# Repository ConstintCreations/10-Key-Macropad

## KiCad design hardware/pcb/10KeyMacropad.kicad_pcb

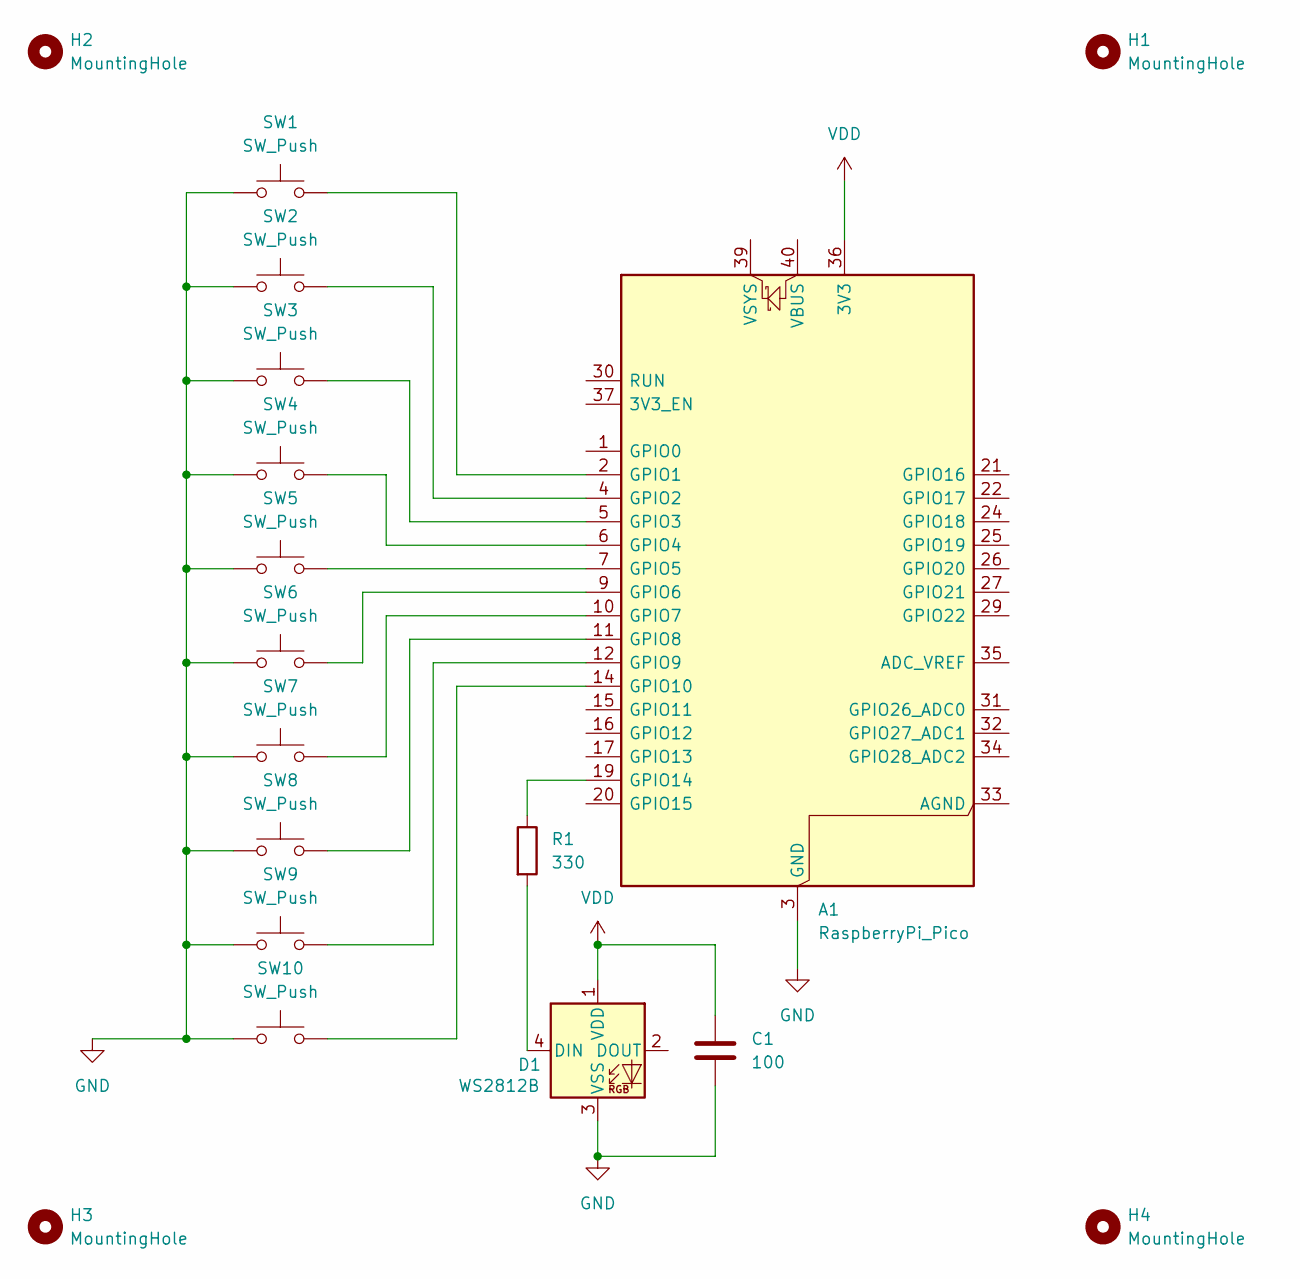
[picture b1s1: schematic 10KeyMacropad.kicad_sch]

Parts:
A1: RaspberryPi_Pico; PinHeader_2x20_P2.54mm_Vertical
C1: 100; CP_Radial_D5.0mm_P2.00mm
D1: WS2812B; LED_WS2812B_PLCC4_5.0x5.0mm_P3.2mm
H1, H2, H3, H4: MountingHole; MountingHole_3.2mm_M3
R1: 330; R_Axial_DIN0207_L6.3mm_D2.5mm_P10.16mm_Horizontal
SW1, SW2, SW3, SW4, SW5, SW6, SW7, SW8, SW9, SW10: SW_Push; MX-Hotswap-1U

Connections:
GND: A1.3 (GND), A1.8 (GND), A1.13 (GND), A1.18 (GND), A1.23 (GND), A1.28 (GND), A1.38 (GND), C1.2, D1.3 (VSS), SW1.1, SW2.1, SW3.1, SW4.1, SW5.1, SW6.1, SW7.1, SW8.1, SW9.1, SW10.1
unnamed: A1.2 (GPIO1), SW1.2
unnamed: A1.4 (GPIO2), SW2.2
unnamed: A1.5 (GPIO3), SW3.2
unnamed: A1.6 (GPIO4), SW4.2
unnamed: A1.7 (GPIO5), SW5.2
unnamed: A1.9 (GPIO6), SW6.2
unnamed: A1.10 (GPIO7), SW7.2
unnamed: A1.11 (GPIO8), SW8.2
unnamed: A1.12 (GPIO9), SW9.2
unnamed: A1.14 (GPIO10), SW10.2
unnamed: A1.19 (GPIO14), R1.1
unnamed: D1.4 (DIN), R1.2
VDD: A1.36 (3V3), C1.1, D1.1 (VDD)

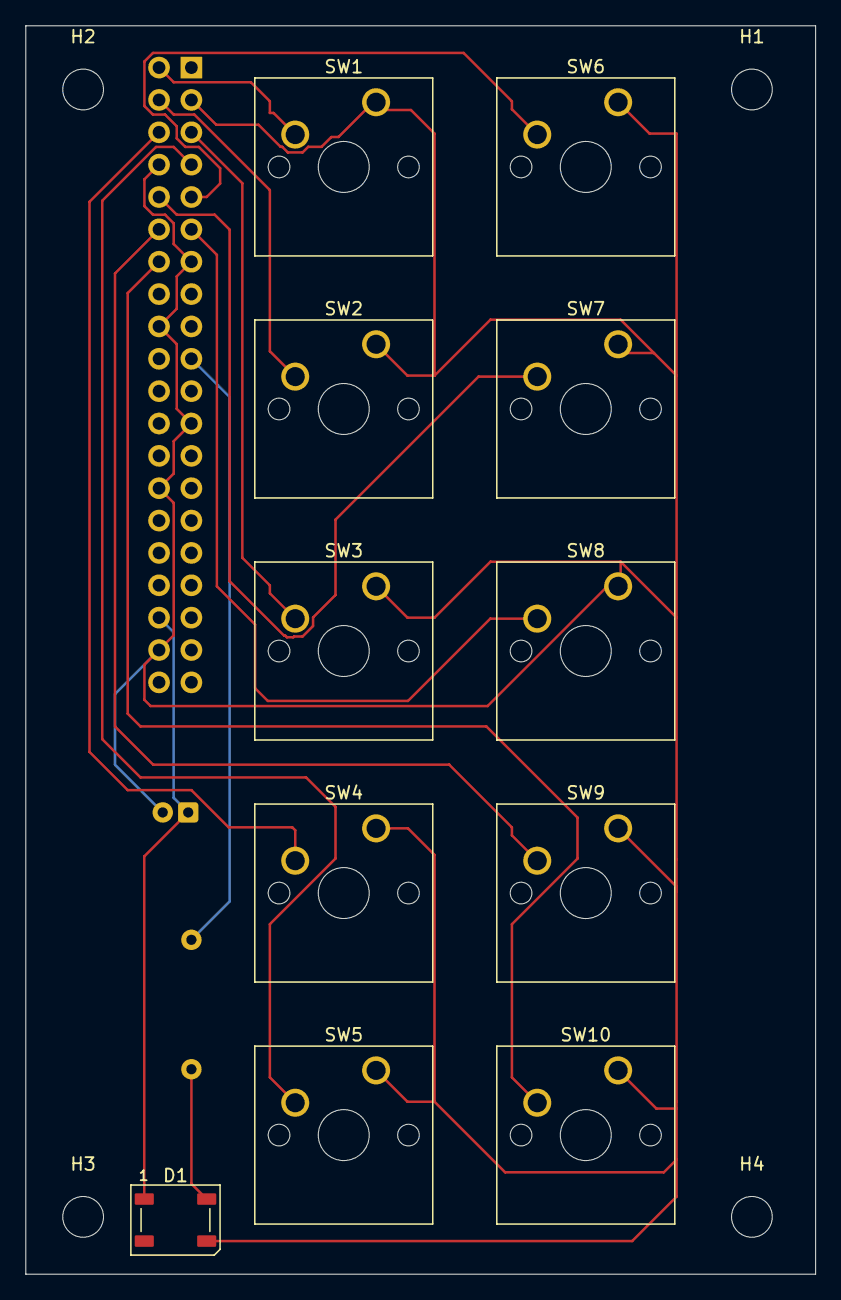
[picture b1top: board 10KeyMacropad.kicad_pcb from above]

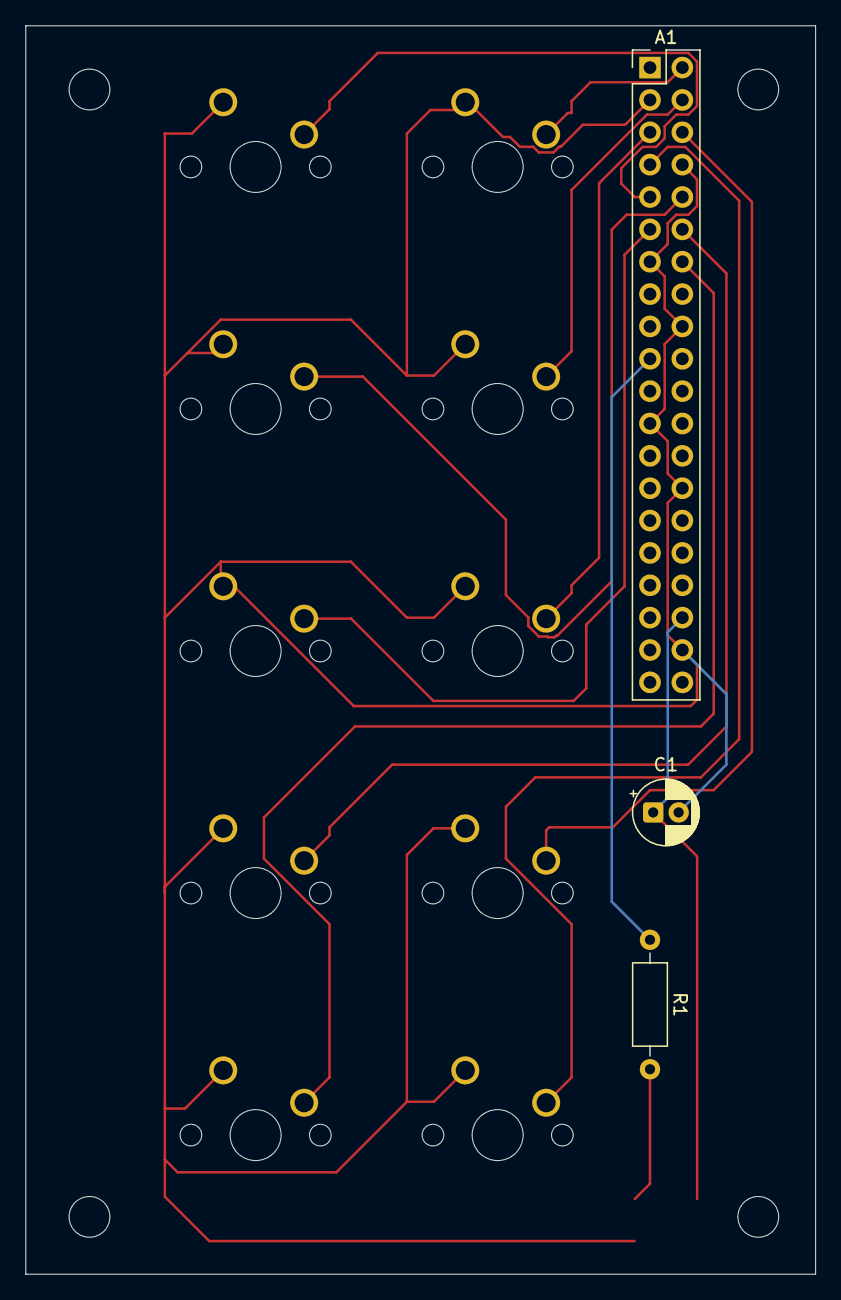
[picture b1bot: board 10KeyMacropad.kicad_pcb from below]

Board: 2 copper layers, 62.0 x 98.0 mm, 18 parts (3 on the bottom side), 14 nets.
